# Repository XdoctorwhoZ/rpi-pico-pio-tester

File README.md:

# rpi-pico-pio-tester
Project to test Raspberry Pi Pico pio

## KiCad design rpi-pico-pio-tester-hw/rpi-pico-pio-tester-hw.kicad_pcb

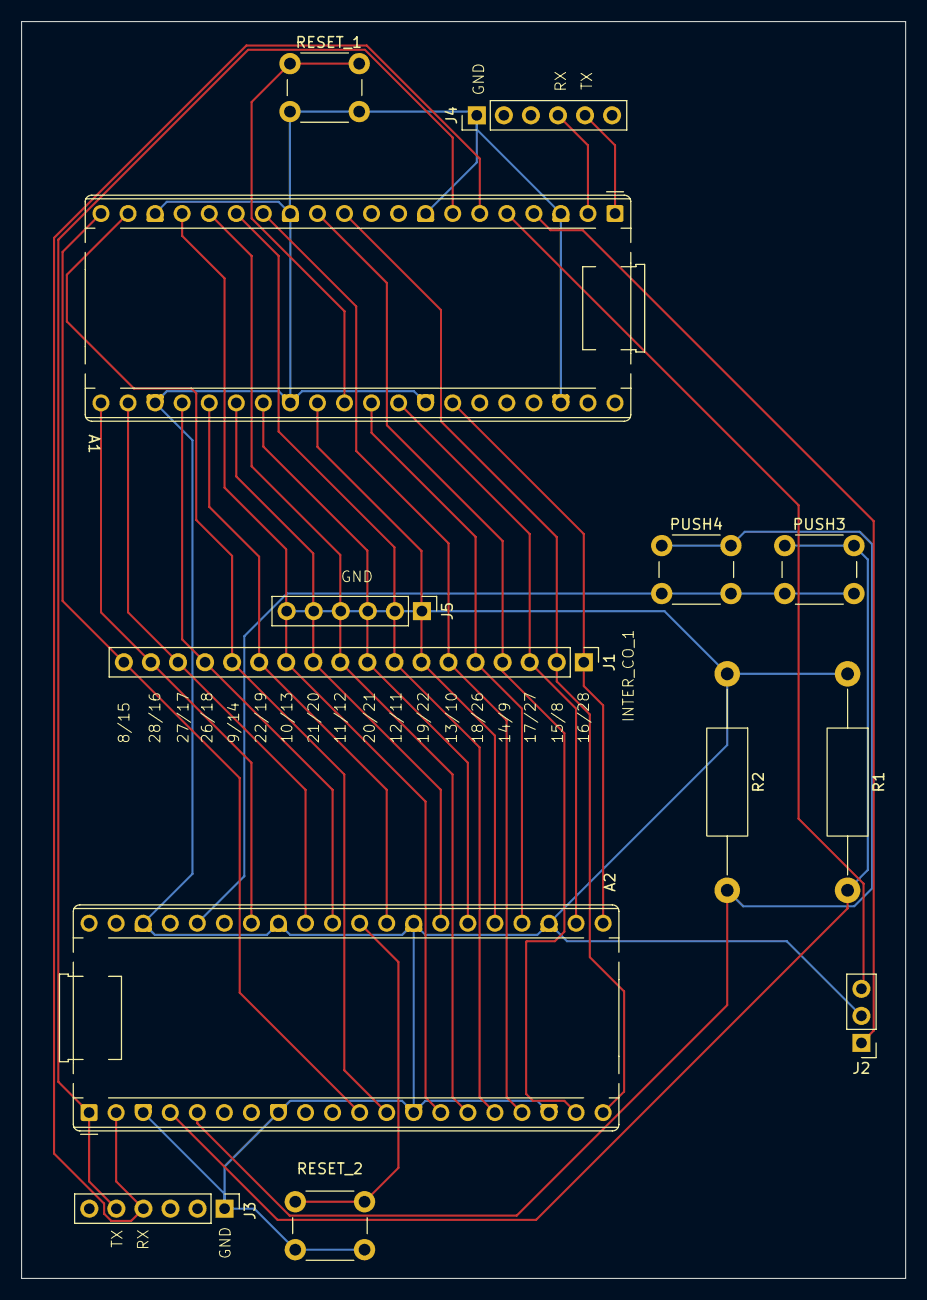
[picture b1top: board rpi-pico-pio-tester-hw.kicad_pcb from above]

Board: 2 copper layers, 83.0 x 118.0 mm, 13 parts (0 on the bottom side), 30 nets.

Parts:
A1: Pico_1; RaspberryPi_Pico_Common_THT
A2: Pico_2; RaspberryPi_Pico_Common_THT
J1: Conn_01x18; PinHeader_1x18_P2.54mm_Vertical
J2: Conn_01x03; PinHeader_1x03_P2.54mm_Vertical
J3: UART_DEBUG_PICO2; PinHeader_1x06_P2.54mm_Vertical
J4: UART_DEBUG_PICO1; PinHeader_1x06_P2.54mm_Vertical
J5: GND; PinHeader_1x06_P2.54mm_Vertical
PUSH3: USR PUSH 1 PICO 2; SW_PUSH_6mm_H5mm
PUSH4: USR PUSH 2 PICO 2; SW_PUSH_6mm_H5mm
R1, R2: R 10Kohm; R_Axial_DIN0411_L9.9mm_D3.6mm_P20.32mm_Horizontal
RESET_1: PUSH RESET PICO 1; SW_PUSH_6mm_H5mm
RESET_2: PUSH RESET PICO 2; SW_PUSH_6mm_H5mm

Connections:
GND: A1.3 (GND), A1.8 (GND), A1.13 (GND), A1.18 (GND), A1.23 (GND), A1.28 (GND), A1.33 (AGND), A1.38 (GND), A2.3 (GND), A2.8 (GND), A2.13 (GND), A2.18 (GND), A2.23 (GND), A2.28 (GND), A2.33 (AGND), A2.38 (GND), J2.2, J3.1, J4.1, J5.1, J5.2, J5.3, J5.4, J5.5, J5.6, R1.1, R2.1, RESET_1.2, RESET_2.2
INTERCO_1: A1.34 (GPIO28), A2.21 (GPIO16), J1.1
INTERCO_2: A1.11 (GPIO8), A2.20 (GPIO15), J1.2
INTERCO_3: A1.32 (GPIO27), A2.22 (GPIO17), J1.3
INTERCO_4: A1.12 (GPIO9), A2.19 (GPIO14), J1.4
INTERCO_5: A1.31 (GPIO26), A2.24 (GPIO18), J1.5
INTERCO_6: A1.14 (GPIO10), A2.17 (GPIO13), J1.6
INTERCO_7: A1.29 (GPIO22), A2.25 (GPIO19), J1.7
INTERCO_8: A1.15 (GPIO11), A2.16 (GPIO12), J1.8
INTERCO_9: A1.27 (GPIO21), A2.26 (GPIO20), J1.9
INTERCO_10: A1.16 (GPIO12), A2.15 (GPIO11), J1.10
INTERCO_11: A1.26 (GPIO20), A2.27 (GPIO21), J1.11
INTERCO_12: A1.17 (GPIO13), A2.14 (GPIO10), J1.12
INTERCO_13: A1.25 (GPIO19), A2.29 (GPIO22), J1.13
INTERCO_14: A1.19 (GPIO14), A2.12 (GPIO9), J1.14
INTERCO_15: A1.24 (GPIO18), A2.31 (GPIO26), J1.15
INTERCO_16: A1.22 (GPIO17), A2.32 (GPIO27), J1.16
INTERCO_17: A1.21 (GPIO16), A2.34 (GPIO28), J1.17
INTERCO_18: A1.20 (GPIO15), A2.11 (GPIO8), J1.18
IO_USR_BP_1: A2.4 (GPIO2), PUSH3.1, R1.2
IO_USR_BP_2: A2.5 (GPIO3), PUSH4.1, R2.2
PICO_1_RUN: A1.30 (RUN), RESET_1.1
PICO_1_UART_RX: A1.2 (UART0_RX), J4.4
PICO_1_UART_TX: A1.1 (UART0_TX), J4.5
PICO_2_3V3: A2.36 (3V3), PUSH3.2, PUSH4.2
PICO_2_RUN: A2.30 (RUN), RESET_2.1
PICO_2_SWCLK: A1.4 (GPIO2), J2.1
PICO_2_SWDIO: A1.5 (GPIO3), J2.3
PICO_2_UART_RX: A1.6 (UART1_TX), A2.2 (UART0_RX), J3.4
PICO_2_UART_TX: A1.7 (UART1_RX), A2.1 (UART0_TX), J3.5

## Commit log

2026-05-22 start pcb design
2026-05-22 import pico lib
2026-05-22 remove external libs
2026-05-23 pico and ocnnection still need some checks
2026-05-23 end of schematic
2026-05-26 go back on schem, change interco to ease layout
2026-05-27 pcb almost ok, need serigraphy
2026-05-27 hw ready
2026-05-27 create fabrication files
2026-05-27 save all
